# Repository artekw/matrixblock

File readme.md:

# matrixblock

The goal of this project is create a cape for BeagleBone Black to drive a [Sure Electronic 32x16 LED Display](http://www.sureelectronics.net/goods.php?id=1095).

## Hardware Connection

Power circuit from matrix connector, not BeagleBone! Use power adapter 5V/2A.

## Compile the code

TODO

Examples:

    $ cd examples
    $ make
    $ ./test

Clock:

    $ make
    $ ./clock

### TODO

- python bindings or TCP deamon

### DONE

- print static text
- scroll text
- set brightness (in range 0-16)
- schematics and PCB design of cape
- DT code and EEEPROM firmware
- add RTC clock

### Source

Based on source code from https://github.com/dcuartielles/HT1632c

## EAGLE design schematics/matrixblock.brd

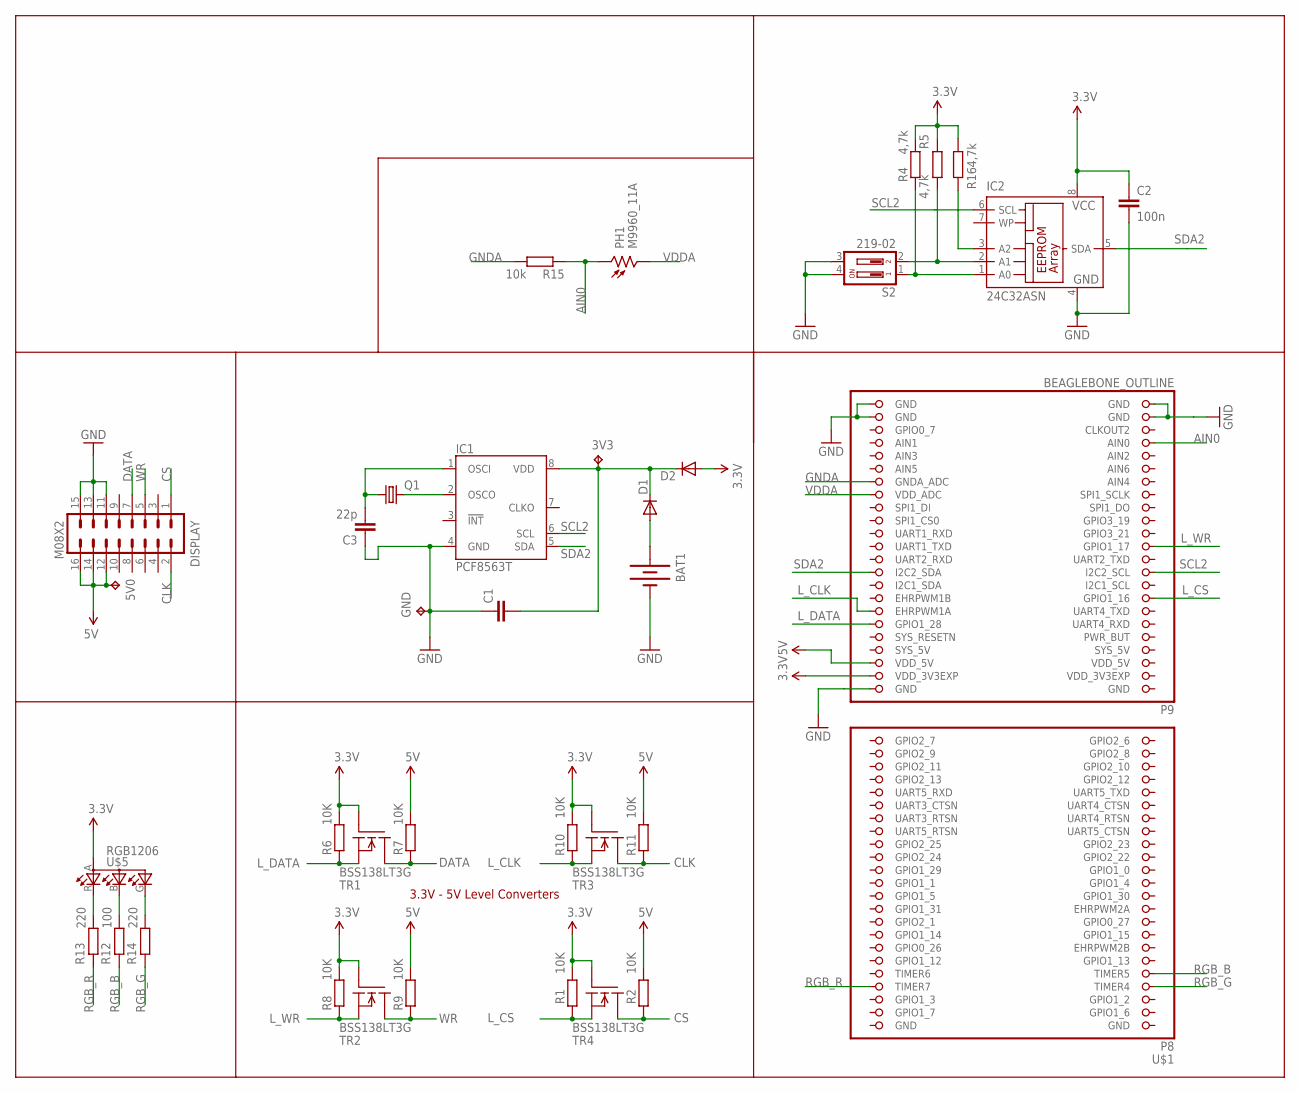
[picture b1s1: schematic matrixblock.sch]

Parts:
3V3, 5V0: TPTP20R; TP20R
BAT1: BATTERY20PTH; BATTCOM_20MM_PTH
C1: C-EUC0805; C0805
C2: 100n; C0805
C3: 22p; C0805
D1, D2: DIODEHV; DIODE-HV
DISPLAY: M08X2; 2X8
GND: TPTP20R; TP20R
IC1: PCF8563T; SO8
IC2: 24C32ASN; SO-08
PH1: M9960_11A; M9960
Q1: CRYSTALTC26H; TC26H
R1, R2, R6, R7, R8, R9, R10, R11: 10K; R0805
R4, R5, R16: 4,7k; R0805
R12: 100; R0805
R13, R14: 220; R0805
R15: 10k; R0805
S2: 219-02; CTS-219-02
TR1, TR2, TR3, TR4: BSS138LT3G; SOT23
U$1: BEAGLEBONE_OUTLINE; BEAGLEBONE_SHIELD
U$5: RGB1206

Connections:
3.3V: D2.A, R1.1, R6.1, R8.1, R10.1, TR1.1 (G), TR2.1 (G), TR3.1 (G), TR4.1 (G), U$1.50 (VDD_3V3EXP), U$5.A
5V: 5V0.TP, DISPLAY.12, DISPLAY.14, DISPLAY.16, R2.1, R7.1, R9.1, R11.1, U$1.52 (VDD_5V)
AIN0: PH1.1, R15.2, U$1.85 (AIN0)
CLK: DISPLAY.2, R11.2, TR3.3 (D)
CS: DISPLAY.1, R2.2, TR4.3 (D)
DATA: DISPLAY.7, R7.2, TR1.3 (D)
GND: BAT1.2 (-), C1.1, C2.2, C3.1, DISPLAY.11, DISPLAY.13, DISPLAY.15, GND.TP, IC1.4 (GND), IC2.4 (GND), S2.3, S2.4, U$1.1 (GND), U$1.2 (GND), U$1.47 (GND), U$1.48 (GND), U$1.89 (GND), U$1.90 (GND), U$1.91 (GND), U$1.92 (GND)
GNDA: R15.1, U$1.80 (GNDA_ADC)
L_CLK: R10.2, TR3.2 (S), U$1.60 (EHRPWM1A)
L_CS: R1.2, TR4.2 (S), U$1.61 (GPIO1_16)
L_DATA: R6.2, TR1.2 (S), U$1.58 (GPIO1_28)
L_WR: R8.2, TR2.2 (S), U$1.69 (GPIO1_17)
unnamed: BAT1.1 (+), D1.A
unnamed: R12.1, U$5.B (CBLUE)
unnamed: IC1.2 (OSCO), Q1.2
unnamed: C3.2, IC1.1 (OSCI), Q1.1
unnamed: R13.1, U$5.R (CRED)
unnamed: 3V3.TP, C1.2, D1.C, D2.C, IC1.8 (VDD)
unnamed: R14.1, U$5.G (CGREEN)
unnamed: IC2.3 (A2), R16.2
unnamed: IC2.2 (A1), R5.1, S2.2
unnamed: IC2.1 (A0), R4.2, S2.1
RGB_B: R12.2, U$1.9 (TIMER5)
RGB_G: R14.2, U$1.7 (TIMER4)
RGB_R: R13.2, U$1.8 (TIMER7)
SCL2: IC1.6 (SCL), IC2.6 (SCL), U$1.65 (I2C2_SCL)
SDA2: IC1.5 (SDA), IC2.5 (SDA), U$1.66 (I2C2_SDA)
SYS_5V: U$1.53 (SYS_5V)
VCC: C2.1, IC2.8 (VCC), R4.1, R5.2, R16.1
VDDA: PH1.2, U$1.78 (VDD_ADC)
VDD_3V3EXP: U$1.49 (VDD_3V3EXP)
VDD_5V: U$1.51 (VDD_5V)
WR: DISPLAY.5, R9.2, TR2.3 (D)

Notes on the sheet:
3.3V - 5V Level Converters

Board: 2 copper layers, 36 parts (1 on the bottom side), 30 nets, no tracks yet.

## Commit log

2013-09-14 fetch code from https://github.com/larmoreg/ece497 Now we need to clean up and write python bindings
2013-09-14 add some example
2013-09-14 add required headers
2013-09-14 display DE-DP14112 have 32 pixels width
2013-09-14 some warning about code
2013-09-14 clean up example
2013-09-14 another implementation
2013-09-15 submit working code, still need clean up
2013-09-15 not needed
2013-09-15 dts file
2013-09-15 fix dts name file
2013-09-17 Correct pins
2013-09-17 gitignore file
2013-09-17 extend readme file
2013-09-17 typos...
2013-09-21 fonts works
2013-09-21 display font works
2013-09-21 uncomment important things
2013-09-21 cleanup, extend readme
2013-09-21 test message
2013-09-21 some optimalization
2013-09-21 gpio export checking, no more debug message im dmesg
2013-09-21 add brightness control via command line argument
2013-09-21 link to matrix
2013-09-22 add example, create feature deamon
2013-09-22 extend readme
2013-09-22 sync current work
2013-09-22 current work
2013-09-22 fix ain
2013-09-22 fix ain #2
2013-10-06 rename directory
2013-10-06 Preliminary implementation HT1632c driver in Python
2013-10-06 Import of modified files originally from http://pignology.net/ Changes are:
    * Enabled UART 2,3,5
    * Added pin mux configuration for the aformentioned UARTS
    and disabled heatbeat at usr0 LED(by me)
2013-10-06 add led systemd service
2013-10-06 PCF8563 as hadware RTC
2013-10-12 full hours on green, temporary change a gpios define
2013-10-12 Infinite server
2013-10-12 rewrite BoneHeader
2013-10-12 rename file; change colors
2013-10-22 update DT file; add eeeprom firmware
2013-10-22 schematics
2013-10-22 update todo and done :)
2013-10-22 typos
2013-10-22 Almost all work, but slow expecially scroll text
2016-01-08 Update DTS file

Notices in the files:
parts and their libraries:
SparkFun-Connectors: Licensing: CC v3.0 Share-Alike You are welcome to use this library for commercial purposes.
